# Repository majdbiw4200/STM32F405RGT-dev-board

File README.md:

# STM32F405RGT-dev-board
STM32 + USB + Buck Converter PCB Design

This Project was made to make a dev board for STM32F405RGT microcontroller with USB, buck converter, I2C, UART and SPI

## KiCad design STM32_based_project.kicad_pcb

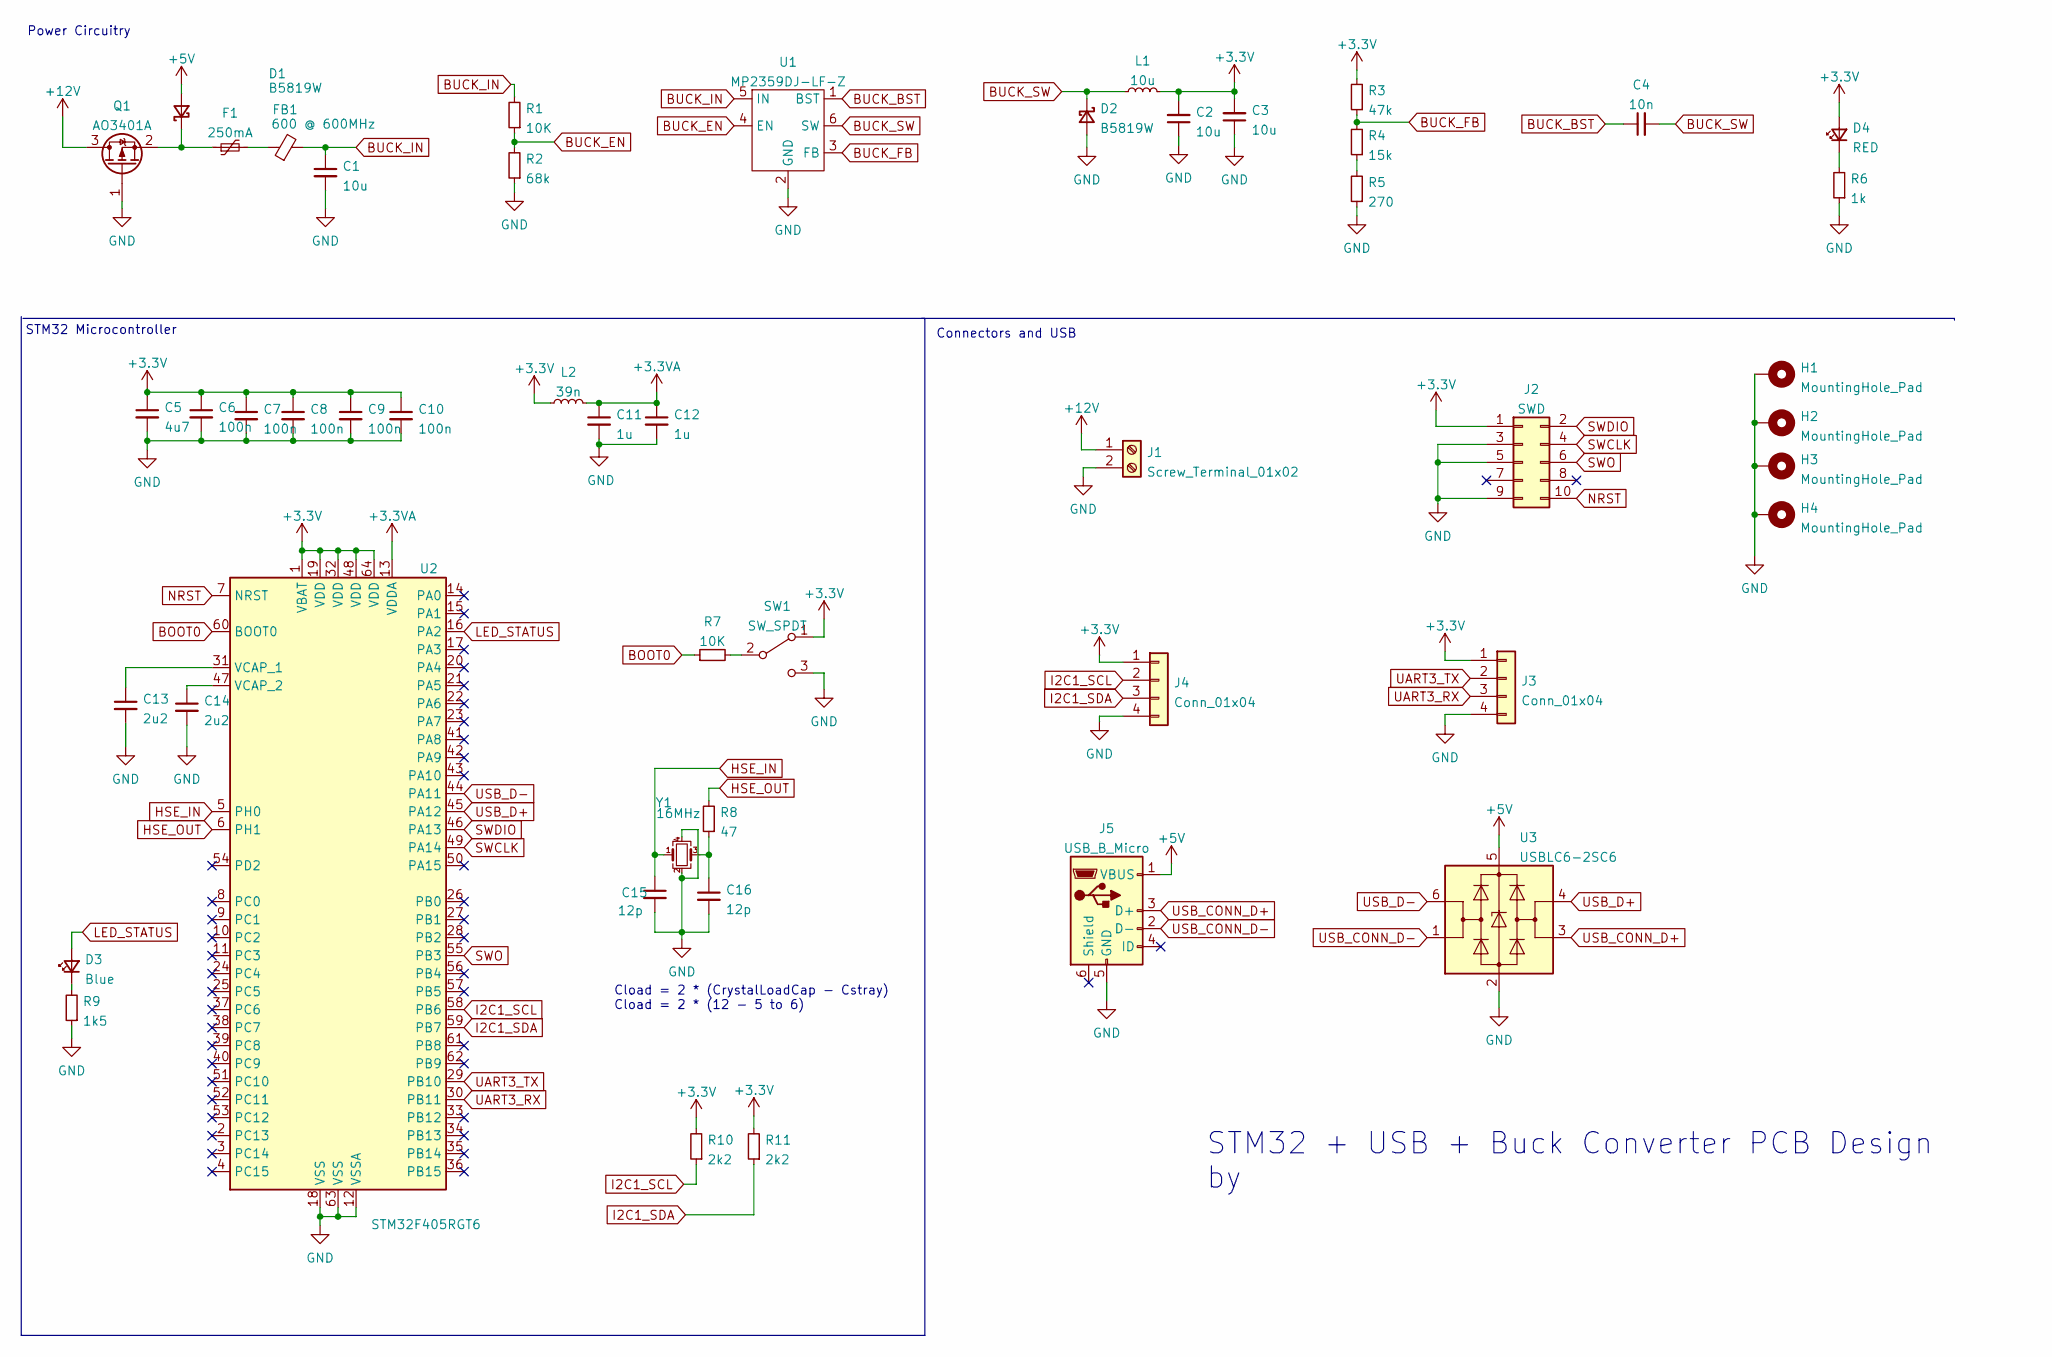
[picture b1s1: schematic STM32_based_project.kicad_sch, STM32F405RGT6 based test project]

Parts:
C1, C2, C3: 10u; C_1206_3216Metric; LCSC Part # C13585
C4: 10n; C_0603_1608Metric; LCSC Part # C57112
C5: 4u7; C_0603_1608Metric; LCSC Part # C19666
C6, C7, C8, C9, C10: 100n; C_0402_1005Metric; LCSC Part # C307331
C11, C12: 1u; C_0402_1005Metric; LCSC Part # C52923
C13, C14: 2u2; C_0603_1608Metric; LCSC Part # C23630
C15, C16: 12p; C_0402_1005Metric; LCSC Part # C1547
D1, D2: B5819W; D_SOD-123; LCSC Part # C8598
D3: Blue; LED_0603_1608Metric; LCSC Part # C138541
D4: RED; LED_0603_1608Metric; LCSC Part # C118330
F1: 250mA; Fuse_1206_3216Metric; LCSC Part # C99561
FB1: 600 @ 600MHz; L_0805_2012Metric; LCSC Part # C1017
H1, H2, H3, H4: MountingHole_Pad; MountingHole_4.3mm_M4_Pad_Via
J1: Screw_Terminal_01x02; TerminalBlock_Phoenix_PT-1,5-2-3.5-H_1x02_P3.50mm_Horizontal
J2: SWD; PinHeader_2x05_P1.27mm_Vertical_SMD
J3, J4: Conn_01x04; Molex_PicoBlade_53048-0410_1x04_P1.25mm_Horizontal
J5: USB_B_Micro; USB_Micro-B_Molex_47346-0001; LCSC Part # C393940
L1: 10u; L_6.3x6.3_H3; LCSC Part # C163676
L2: 39n; L_0402_1005Metric; LCSC Part # C335623
Q1: AO3401A; SOT-23; LCSC Part # C15127
R1: 10K; R_0603_1608Metric; LCSC Part # C25197
R2: 68k; R_0603_1608Metric; LCSC Part # C23231
R3: 47k; R_0603_1608Metric; LCSC Part # C25819
R4: 15k; R_0603_1608Metric; LCSC Part # C22809
R5: 270; R_0603_1608Metric; LCSC Part # C22966
R6: 1k; R_0603_1608Metric; LCSC Part # C21190
R7: 10K; R_0402_1005Metric; LCSC Part # C25744
R8: 47; R_0402_1005Metric; LCSC Part # C25118
R9: 1k5; R_0603_1608Metric; LCSC Part # C22843
R10, R11: 2k2; R_0402_1005Metric; LCSC Part # C25879
SW1: SW_SPDT; SW_SPDT_PCM12; LCSC Part # C109335
U1: MP2359DJ-LF-Z; SOT-23-6; LCSC Part # C14259
U2: STM32F405RGT6; LQFP-64_10x10mm_P0.5mm; LCSC Part # C15742
U3: USBLC6-2SC6; SOT-23-6; LCSC Part # C2827654
Y1: 16MHz; Crystal_SMD_3225-4Pin_3.2x2.5mm; LCSC Part # C160456

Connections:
+3.3VA: C11.1, C12.1, L2.2, U2.13 (VDDA)
+3V3: C2.2, C3.2, C5.1, C6.1, C7.1, C8.1, C9.1, C10.1, D4.2 (A), J2.1, J3.1, J4.1, L1.2, L2.1, R3.2, R10.2, R11.2, SW1.1 (A), U2.1 (VBAT), U2.19 (VDD), U2.32 (VDD), U2.48 (VDD), U2.64 (VDD)
+5V: D1.2 (A), J5.1 (VBUS), U3.5 (VBUS)
+12V: J1.1, Q1.3 (D)
BOOT0: R7.1, U2.60 (BOOT0)
BUCK_BST: C4.1, U1.1 (BST)
BUCK_EN: R1.1, R2.2, U1.4 (EN)
BUCK_FB: R3.1, R4.2, U1.3 (FB)
BUCK_IN: C1.1, FB1.2, R1.2, U1.5 (IN)
BUCK_SW: C4.2, D2.1 (K), L1.1, U1.6 (SW)
GND: C1.2, C2.1, C3.1, C5.2, C6.2, C7.2, C8.2, C9.2, C10.2, C11.2, C12.2, C13.2, C14.2, C15.2, C16.2, D2.2 (A), H1.1, H2.1, H3.1, H4.1, J1.2, J2.3, J2.5, J2.9, J3.4, J4.4, J5.5 (GND), Q1.1 (G), R2.1, R5.1, R6.1, R9.1, SW1.3 (C), U1.2 (GND), U2.12 (VSSA), U2.18 (VSS), U2.63 (VSS), U3.2 (GND), Y1.2, Y1.4
HSE_IN: C15.1, U2.5 (PH0), Y1.1
HSE_OUT: R8.2, U2.6 (PH1)
I2C1_SCL: J4.2, R10.1, U2.58 (PB6)
I2C1_SDA: J4.3, R11.1, U2.59 (PB7)
LED_STATUS: D3.2 (A), U2.16 (PA2)
NRST: J2.10, U2.7 (NRST)
unnamed: C13.1, U2.31 (VCAP_1)
unnamed: C14.1, U2.47 (VCAP_2)
unnamed: C16.1, R8.1, Y1.3
unnamed: D1.1 (K), F1.1, Q1.2 (S)
unnamed: D3.1 (K), R9.2
unnamed: D4.1 (K), R6.2
unnamed: F1.2, FB1.1
unnamed: R4.1, R5.2
unnamed: R7.2, SW1.2 (B)
SWCLK: J2.4, U2.49 (PA14)
SWDIO: J2.2, U2.46 (PA13)
SWO: J2.6, U2.55 (PB3)
UART3_RX: J3.3, U2.30 (PB11)
UART3_TX: J3.2, U2.29 (PB10)
USB_CONN_D+: J5.3 (D+), U3.3 (I/O2)
USB_CONN_D-: J5.2 (D-), U3.1 (I/O1)
USB_D+: U2.45 (PA12), U3.4 (I/O2)
USB_D-: U2.44 (PA11), U3.6 (I/O1)

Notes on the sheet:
Power Circuitry
STM32 Microcontroller
Cload = 2 * (CrystalLoadCap - Cstray) Cload = 2 * (12 - 5 to 6)
STM32 + USB + Buck Converter PCB Design by
Connectors and USB

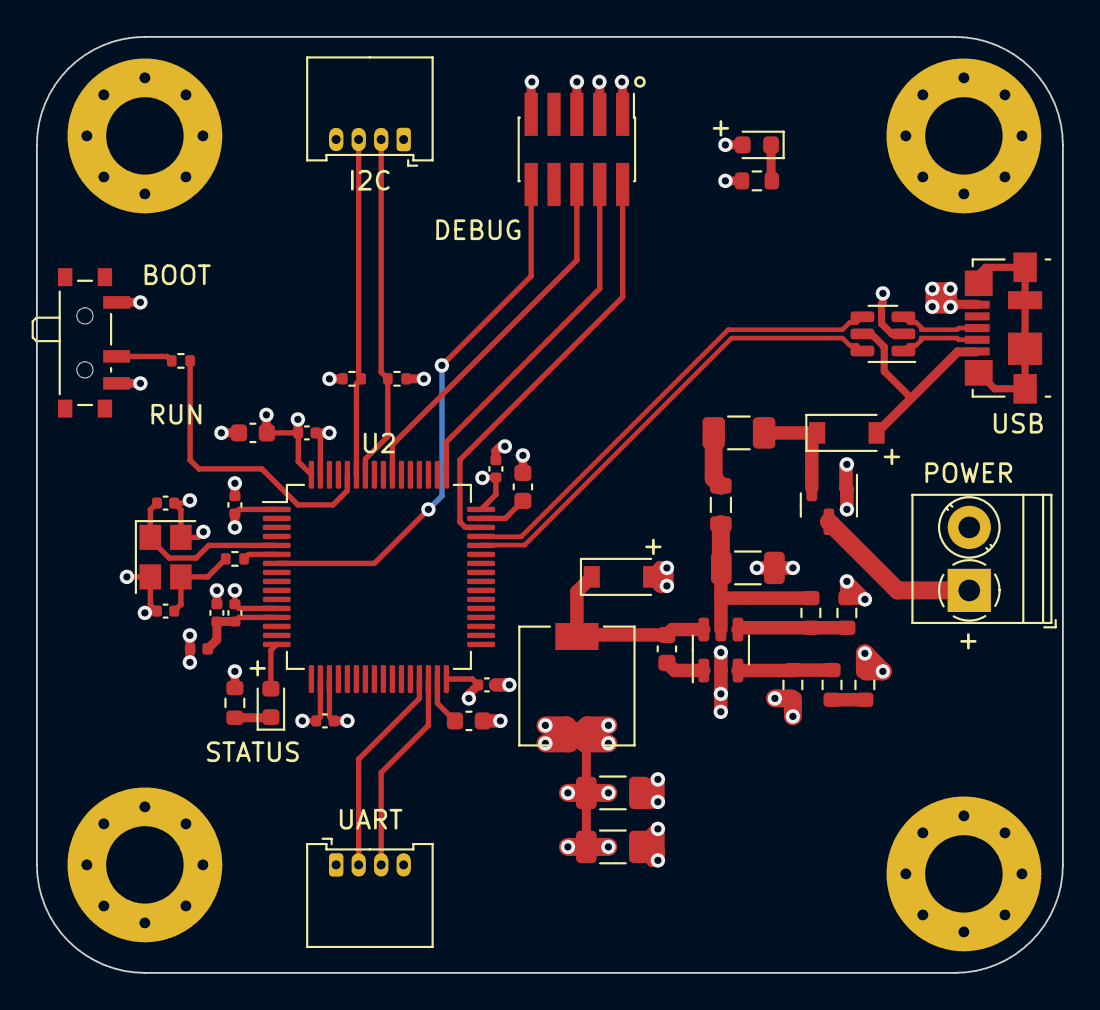
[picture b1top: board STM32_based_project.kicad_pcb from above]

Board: 4 copper layers, 57.0 x 52.0 mm, 50 parts (0 on the bottom side), 35 nets.

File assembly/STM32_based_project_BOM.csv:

Comment,Designator,Footprint,LCSC Part #
"10u Unpolarized capacitor, small symbol","C1,C2,C3",C_1206_3216Metric,
"10n Unpolarized capacitor, small symbol",C4,C_0603_1608Metric,
"4u7 Unpolarized capacitor, small symbol",C5,C_0603_1608Metric,
"100n Unpolarized capacitor, small symbol","C6,C7,C8,C9,C10",C_0402_1005Metric,
"1u Unpolarized capacitor, small symbol","C11,C12",C_0402_1005Metric,
"2u2 Unpolarized capacitor, small symbol","C13,C14",C_0603_1608Metric,
"12p Unpolarized capacitor, small symbol","C15,C16",C_0402_1005Metric,
"B5819W Schottky diode, small symbol","D1,D2",D_SOD-123,
"Blue Light emitting diode, small symbol",D3,LED_0603_1608Metric,
"RED Light emitting diode, small symbol",D4,LED_0603_1608Metric,
"250mA Resettable fuse, polymeric positive temperature coefficient, small symbol",F1,Fuse_1206_3216Metric,
"600 @ 600MHz Ferrite bead, small symbol",FB1,L_0805_2012Metric,
MountingHole_Pad Mounting Hole with connection,"H1,H2,H3,H4",MountingHole_4.3mm_M4_Pad_Via,
"Screw_Terminal_01x02 Generic screw terminal, single row, 01x02, script generated (kicad-library-utils/schlib/autogen/connector/)",J1,"TerminalBlock_Phoenix_PT-1,5-2-3.5-H_1x02_P3.50mm_Horizontal",
"SWD Generic connector, double row, 02x05, odd/even pin numbering scheme (row 1 odd numbers, row 2 even numbers), script generated (kicad-library-utils/schlib/autogen/connector/)",J2,PinHeader_2x05_P1.27mm_Vertical_SMD,
"Conn_01x04 Generic connector, single row, 01x04, script generated (kicad-library-utils/schlib/autogen/connector/)","J3,J4",Molex_PicoBlade_53048-0410_1x04_P1.25mm_Horizontal,
USB_B_Micro USB Micro Type B connector,J5,USB_Micro-B_Molex_47346-0001,
"10u Inductor, small symbol",L1,L_6.3x6.3_H3,
"39n Inductor, small symbol",L2,L_0402_1005Metric,
"AO3401A -4.0A Id, -30V Vds, P-Channel MOSFET, SOT-23",Q1,SOT-23,
"10K Resistor, small symbol",R1,R_0603_1608Metric,
"68k Resistor, small symbol",R2,R_0603_1608Metric,
"47k Resistor, small symbol",R3,R_0603_1608Metric,
"15k Resistor, small symbol",R4,R_0603_1608Metric,
"270 Resistor, small symbol",R5,R_0603_1608Metric,
"1k Resistor, small symbol",R6,R_0603_1608Metric,
"10K Resistor, small symbol",R7,R_0402_1005Metric,
"47 Resistor, small symbol",R8,R_0402_1005Metric,
"1k5 Resistor, small symbol",R9,R_0603_1608Metric,
"2k2 Resistor, small symbol","R10,R11",R_0402_1005Metric,
"SW_SPDT Switch, single pole double throw",SW1,SW_SPDT_PCM12,
MP2359DJ-LF-Z ,U1,SOT-23-6,
"STM32F405RGT6 ARM Cortex-M4 MCU, 1024KB flash, 128KB RAM, 168MHz, 1.8-3.6V, 51 GPIO, LQFP-64",U2,LQFP-64_10x10mm_P0.5mm,
"USBLC6-2SC6 Very low capacitance ESD protection diode, 2 data-line, SOT-23-6",U3,SOT-23-6,
"16MHz Four pin crystal, GND on pins 2 and 4, small symbol",Y1,Crystal_SMD_3225-4Pin_3.2x2.5mm,

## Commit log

2022-05-20 add the board, assembly and gerber files
